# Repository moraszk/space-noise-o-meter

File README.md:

Móra Space module
=================

Students from Ferenc Mora College for Advanced Studies developed a payload for the MRC-100 satellite. These are the sources of it.

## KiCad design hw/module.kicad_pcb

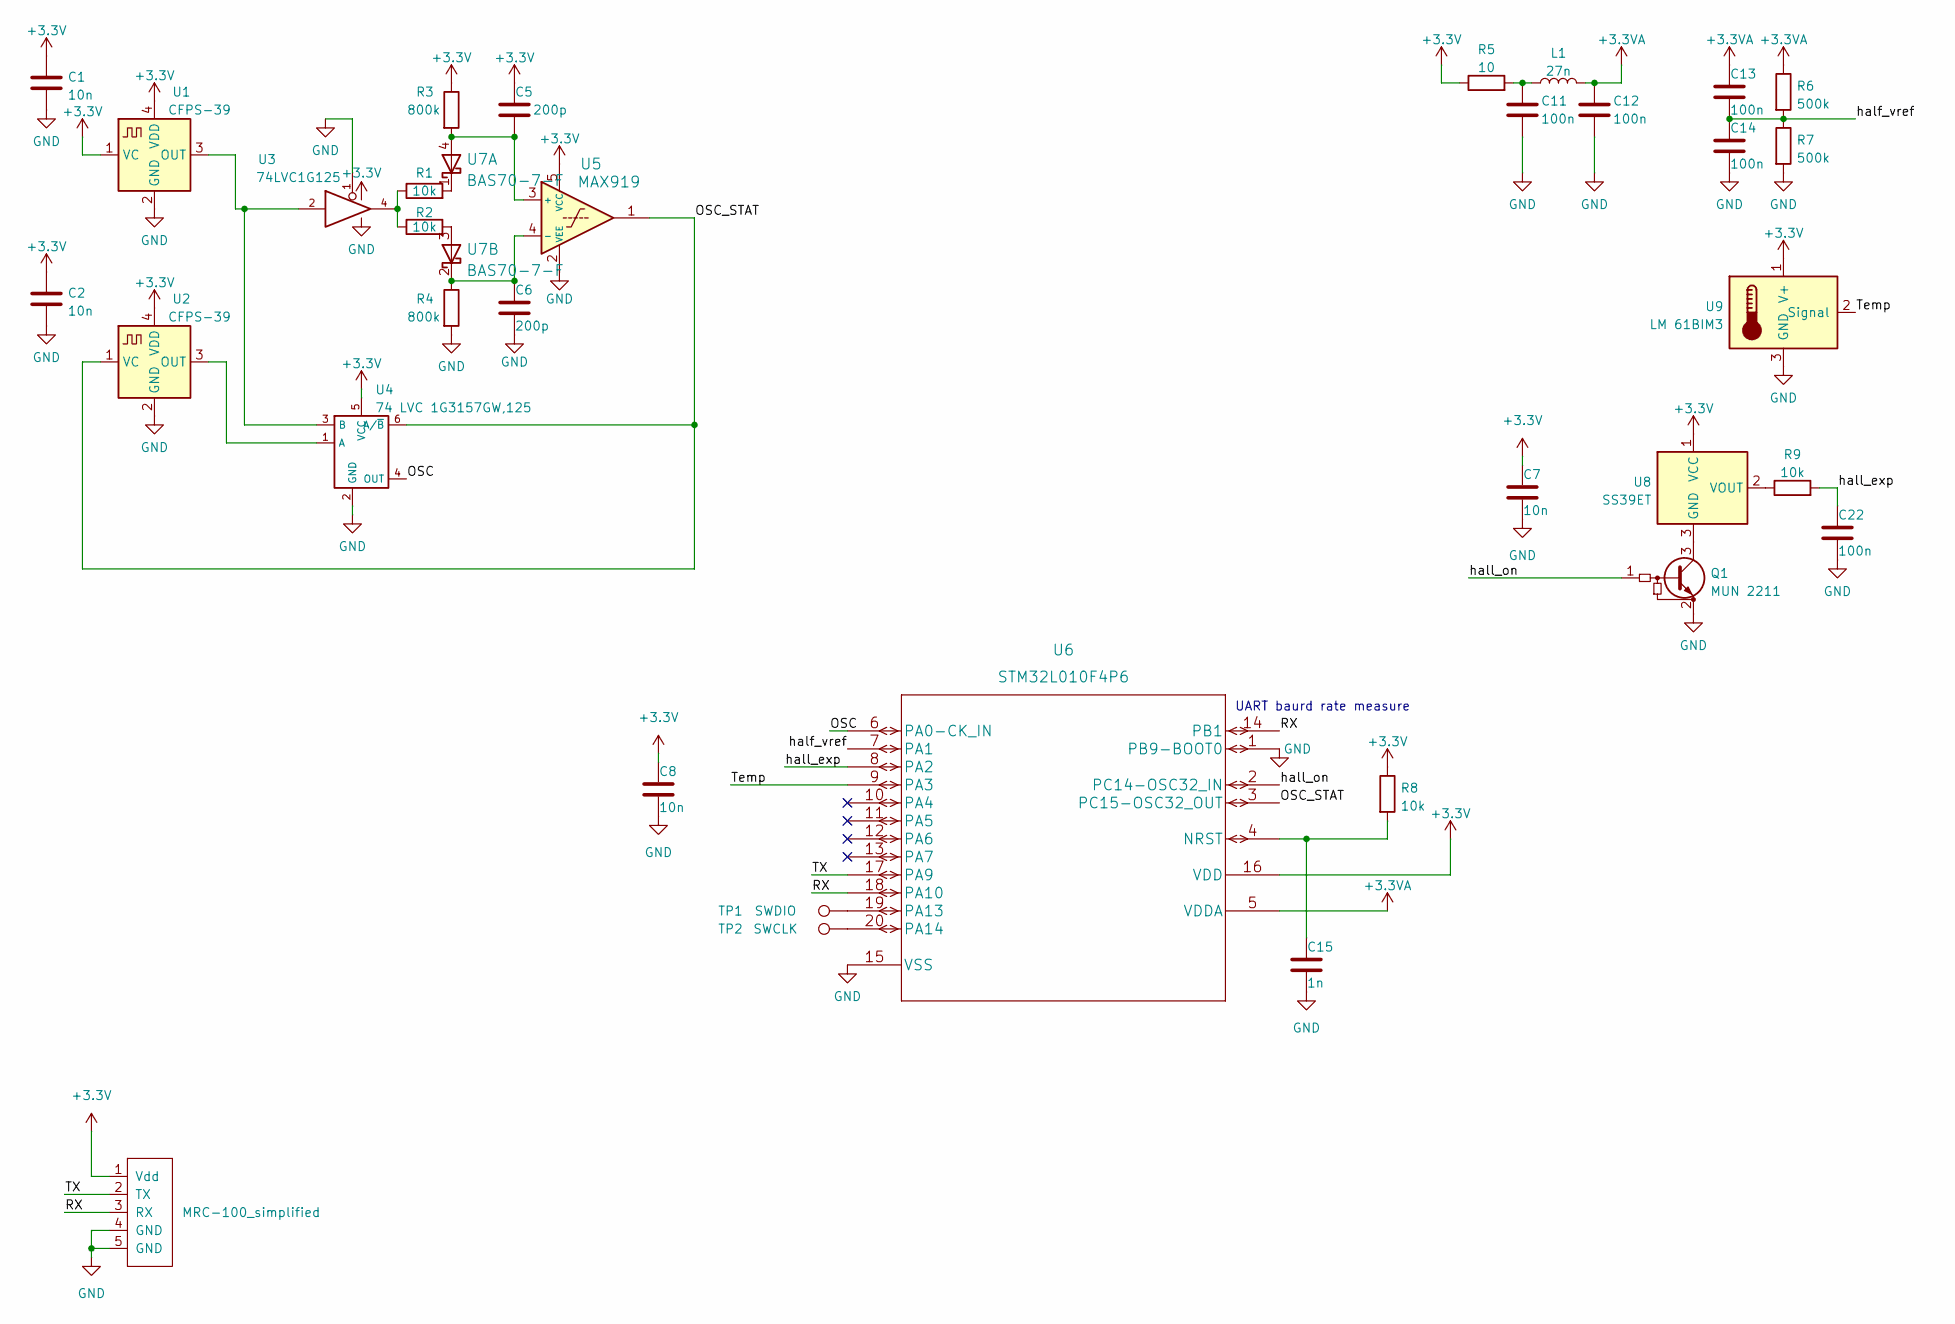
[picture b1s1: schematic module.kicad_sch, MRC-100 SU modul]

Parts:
C1, C2, C7, C8: 10n; C_0603_1608Metric_Pad1.08x0.95mm_HandSolder
C5, C6: 200p; C_0603_1608Metric_Pad1.08x0.95mm_HandSolder
C11, C12, C13, C14, C22: 100n; C_0603_1608Metric_Pad1.08x0.95mm_HandSolder
C15: 1n; C_0603_1608Metric_Pad1.08x0.95mm_HandSolder
Int1: MRC-100_simplified; mrc-100
L1: 27n; L_0603_1608Metric_Pad1.05x0.95mm_HandSolder
Q1: MUN 2211; SOT-23_Handsoldering
R1, R2, R8, R9: 10k; R_0603_1608Metric_Pad0.98x0.95mm_HandSolder
R3, R4: 800k; R_0603_1608Metric_Pad0.98x0.95mm_HandSolder
R5: 10; R_0603_1608Metric_Pad0.98x0.95mm_HandSolder
R6, R7: 500k; R_0603_1608Metric_Pad0.98x0.95mm_HandSolder
TP1: SWDIO; TestPoint_Pad_3.0x3.0mm
TP2: SWCLK; TestPoint_Pad_3.0x3.0mm
U1, U2: CFPS-39; Oscillator_SMD_EuroQuartz_XO32-4Pin_3.2x2.5mm_HandSoldering
U3: 74LVC1G125; SOT-23-5_HandSoldering
U4: 74 LVC 1G3157GW,125; SOT-363_SC-70-6_Handsoldering
U5: MAX919; SOT-23-5_HandSoldering
U6: STM32L010F4P6
U7: BAS70-7-F; SOT-143_Handsoldering
U8: SS39ET; SOT-23_Handsoldering
U9: LM 61BIM3; SOT-23_Handsoldering

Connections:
+3.3V: C1.1, C2.1, C5.1, C7.1, C8.1, Int1.1 (Vdd), R3.1, R5.1, R8.1, U1.1 (VC), U1.4 (VDD), U2.4 (VDD), U3.5 (VCC), U4.5 (VCC), U5.5 (VCC), U6.16 (VDD), U8.1 (VCC), U9.1 (V+)
+3.3VA: C12.1, C13.1, L1.2, R6.1, U6.5 (VDDA)
/OSC: U4.4 (OUT), U6.6 (PA0-CK_IN)
/OSC_STAT: U2.1 (VC), U4.6 (A/~B), U5.1, U6.3 (PC15-OSC32_OUT)
/RX: Int1.3 (RX), U6.14 (PB1), U6.18 (PA10)
/TX: Int1.2 (TX), U6.17 (PA9)
/Temp: U6.9 (PA3), U9.2 (Signal)
/half_vref: C13.2, C14.1, R6.2, R7.1, U6.7 (PA1)
/hall_exp: C22.1, R9.2, U6.8 (PA2)
/hall_on: Q1.1 (B), U6.2 (PC14-OSC32_IN)
GND: C1.2, C2.2, C6.2, C7.2, C8.2, C11.2, C12.2, C14.2, C15.2, C22.2, Int1.4 (GND), Int1.5 (GND), Q1.2 (E), R4.2, R7.2, U1.2 (GND), U2.2 (GND), U3.1, U3.3 (GND), U4.2 (GND), U5.2 (VEE), U6.1 (PB9-BOOT0), U6.15 (VSS), U9.3 (GND)
unnamed: C5.2, R3.2, U5.3 (+), U7.4
unnamed: C6.1, R4.1, U5.4 (-), U7.2
unnamed: C11.1, L1.1, R5.2
unnamed: C15.1, R8.2, U6.4 (NRST)
unnamed: Q1.3 (C), U8.3 (GND)
unnamed: R1.1, R2.1, U3.4
unnamed: R1.2, U7.1
unnamed: R2.2, U7.3
unnamed: R9.1, U8.2 (VOUT)
unnamed: TP1.1, U6.19 (PA13)
unnamed: TP2.1, U6.20 (PA14)
unnamed: U1.3 (OUT), U3.2, U4.3 (B)
unnamed: U2.3 (OUT), U4.1 (A)

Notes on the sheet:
UART baurd rate measure

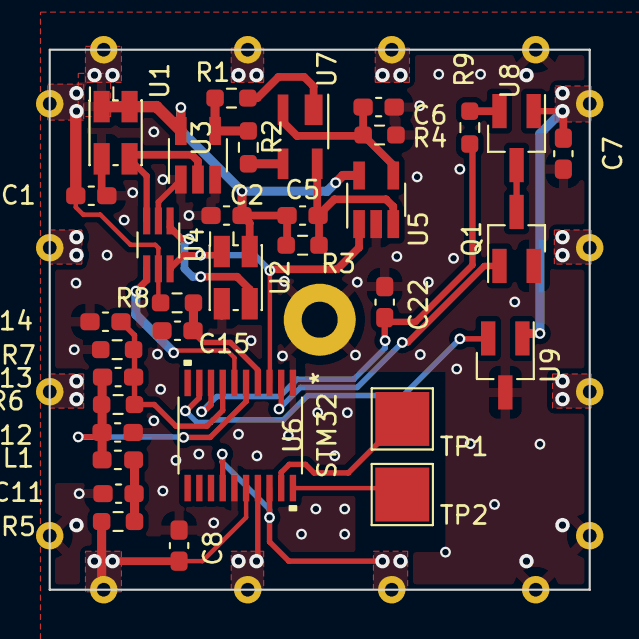
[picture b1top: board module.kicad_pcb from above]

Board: 2 copper layers, 30.0 x 30.0 mm, 35 parts (0 on the bottom side), 24 nets.

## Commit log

2022-10-01 Prepare KiCAD project
2022-10-01 added stm_footprint
2022-10-02 added Max919_footprint
2022-10-02 add changes
2022-10-02 Redraw max919 to conventional symbol
2022-10-02 Update gitignore
2022-10-02 Added redundant oscillator circuit first version
2022-10-02 Placing caps, and stm pinout
2022-10-02 Change oscillator detector resistances
2022-10-02 Add Oscillator detect LTspice simulation
2022-10-02 Border vias added to the PCB
2022-10-02 added mux
2022-10-02 added bas70 symbol
2022-10-02 Rework bas70
2022-10-02 stm32 wiring
2022-10-03 Footprint assignment
2022-10-03 PCB arrange
2022-10-03 PCB wiring
2022-10-04 Pcb++
2022-10-04 Add 3D models
2022-10-04 Footprint fix, and first PCB release
2022-10-05 Final 3D models, final capacitor sizes, final capacitor numbers, final capacitor placements
2022-10-06 Add extra resistor for capacitor measure, remove out-the-board wires
2022-10-06 Software high level functions
2022-10-07 added systemclock config
2022-10-08 added init files
2022-10-09 Add kdev project, dir clean
2022-10-09 Add remaining cmsis headers
2022-10-09 Kdevelop parser configuration
2022-10-09 merge
2022-10-09 Add satellite status
2022-10-09 Fix gpio.hpp types
2022-10-09 Fix cmsis header
2022-10-09 Add makefile for software targets
2022-10-09 Update gitignore with elf
2022-10-09 Status counters at uart
2022-10-09 uart registers and sysclock config
2022-10-10 Add base64 encoder
2022-10-10 qutes nearly finalized
2022-10-10 update gitignores
2022-10-10 Sysclock reapplied
2022-10-10 gpio redone ++
2022-10-10 adc init
2022-10-10 edit adc init
2022-10-11 Reimplement gpio after an unfortunate merge :/
2022-10-11 Document and fix mcu startup process
2022-10-12 Add ring_buffer
2022-10-12 Fix bug in ringbuffer
2022-10-12 Ringbuffer test added
2022-10-12 Fix size_t namespace in ringbuffer
2022-10-12 Update ringbuffer test with emtpy() test
2022-10-13 Fix compilability
2022-10-13 0603 passives
2022-10-14 Add the last wire
2022-10-14 fix assembly extension
2022-10-14 Move via
2022-10-14 Fix status init
2022-10-14 Fix checksum system, and command receiver types, containers
2022-10-14 Extend and fix compiler warnings
2022-10-14 Makefile improvements
2022-10-16 UART timing experiment implemetnation vol. 1
2022-10-17 finalize base64 lookup table
2022-10-17 sw++
2022-10-18 hw init
2022-10-18 telemetry sending
2022-10-18 .hpp files
2022-10-18 Fix char2hex test, upgrade it to uppercase
2022-10-18 Test reentry of telemetry state-machine
2022-10-18 fix chunkid increment
2022-10-18 quotes_test
2022-10-18 Add chunkid to teleemtry
2022-10-18 add telecommand
2022-10-18 Create fuzz test to check for memory safty and valid output of the base64 encoder
2022-10-18 refactor command::destinintion's location, which oscillator in status etc. sw++
2022-10-18 hotfix for compile errors
2022-10-18 telecommands
2022-10-19 memory usage --
2022-10-19 Emplace new in receive buffer memory footprint reduced
2022-10-19 base64 triplet encode stack usage reduced
2022-10-19 reduce main memory footprint
2022-10-19 reduce memory limit in linker script
2022-10-19 Fix tests
2022-10-19 Fix crash on empty input
2022-10-19 Redraw sch for the datasheet
2022-10-19 Add report text
2022-10-19 fix uart init
2022-10-19 Add more fuzz tests
2022-10-19 add doc files
2022-10-19 cont log
2022-10-19 add general description
2022-10-19 remove generated files
2022-10-19 add images
2022-10-19 header setup
2022-10-19 picture rotate
2022-10-20 ADC with DMA
2022-10-20 Add vscode configuration
2022-10-20 Fix local include with angle style
2022-10-20 Add documentation for command destinations
2022-10-20 Add documentation for commands
2022-10-20 Unknown command counter
2022-10-20 Baud measure
2022-10-20 add scope images
2022-10-20 Add Csiha Zrt. to sponsores
2022-10-20 Fix UART GPIO settings
2022-10-20 uart communication worksgit add .!
2022-10-20 add scope images and function table
2022-10-20 edit user commands section
2022-10-20 edit datasheet application section
2022-10-20 add report section
2022-10-20 refresh
2022-10-21 Baud measure works
2022-10-21 add ha8kda cq
2022-10-21 identifier
2022-10-22 uart baud rate experiment fixes
2022-10-22 fix commandreceiver header
2022-10-22 fix telecommand
2022-10-22 fix fallthrough
2022-10-22 refresh the datasheet
2022-10-22 added bom
2022-10-23 change default experiment
2022-10-23 do todo
2022-10-23 adc noise measure complete
2022-10-23 Configure vscode debugger
2022-10-23 vscode c++ recommendations
2022-10-23 Add tictactoe game engine
2022-10-23 controller for tictactoe
2022-10-23 Reset tictactoe board on invalid move
2022-10-23 Implement The Game
2022-10-23 fix adc dma offset
2022-10-23 Translte The Game into English
2022-10-23 extend chunkid
2022-10-23 update tictactoe to use stdarray
2022-10-23 Fix no ack for commands
2022-10-23 Fix missing ack
2022-10-23 fix variable size
2022-10-23 fix uart baud measure
2022-10-23 add hall commands
2022-10-23 Update quotes
2022-10-23 Revert "Fix no ack for commands"
2022-10-23 CMD ACK reimplement
2022-10-23 fix main loop
2022-10-23 fix includes
2022-10-23 fix watchdog
2022-10-24 doc final checks
2022-11-04 added presentation doc
2022-11-05 SW presentation
2022-11-05 Add sponsors
2022-11-05 Add greatings
2022-11-05 change sponsor order by logo height
2022-11-05 typofix
2022-11-05 add sponsors to hw slides
2022-11-05 Set babel
2022-11-11 MRC Day slides
2022-11-26 Ground telemetry parser proof of concept
2022-11-26 Temperature and supply voltage output
2022-11-26 Mora telemetry display
2022-12-28 Redact qutoes
2022-12-28 Add Readme
2022-12-28 Add license (and publish the codes)

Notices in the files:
parts and their libraries:
Copyright 2021 Accelerated Designs. All rights reserved.
